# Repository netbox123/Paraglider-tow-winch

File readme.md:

# Paraglider Tow Winch

Version 0.2

An open-source electric tow winch for paragliding, designed with safety, reliability and maintainability as the primary goals.

The project combines:

- Parametric mechanical design in FreeCAD
- Python-generated CAD models
- Direct rope tension measurement using a load cell
- PID-controlled electric drive
- Automatic level winding using a self-reversing traverse screw
- Open documentation and engineering calculations

## Project Goals

The aim is to build a tow winch that:

- Maintains constant tow force independent of drum diameter.
- Winds the rope neatly during both retrieval and payout.
- Minimizes side loads on the level wind mechanism.
- Is easy to maintain using commercially available components.
- Can be reproduced and improved by other clubs.

## Current Concept

### Frame

- 1500 × 800 × 800 mm
- 50 × 50 × 4 mm square steel tube

### Drum

- Width: 250 mm
- Core diameter: 390 mm
- Flange diameter: 590 mm
- 5 mm steel shell
- 5 mm steel flanges
- 50 mm shaft
- Internal stiffening discs

### Power

Planned motor:

- QS165 12 kW
- 2.37:1 gearbox

### Rope

- 3 mm Dyneema
- Approximately 1500 m
- Typical tow tension: 40–100 kg

### Level Wind

A mechanically synchronized self-reversing traverse screw ("diamond screw" or "level wind screw") is used instead of a stepper motor.

Advantages:

- Works automatically in both winding directions.
- Always remains synchronized with the drum.
- No electronic positioning required.

### Tension Control

Tow force will be measured directly with a load cell mounted beneath the moving guide pulley.

Benefits:

- Direct measurement of rope tension.
- Independent of drum diameter.
- Independent of gearbox efficiency.
- Independent of motor current.
- Improved PID control.

## Software

The FreeCAD model is generated from Python macros (`freecad/`), one module per subsystem, all driven from a single [`config.py`](freecad/config.py).

The intention is that the complete winch can be regenerated from a small set of configuration parameters.

Modules built so far:

- Frame (hollow mitred tube)
- Battery boxes
- Drum (barrel, flanges, shaft, bearings)
- Motor mount and chain drivetrain (motor, sprockets)
- Rope intake (self-aligning swivel, rollers, guide wheels, line cutter)
- Level wind (Hiwin linear rail, self-reversing screw, flange bearings)
- Winding pulley and load cell mount (rod-end pivot)
- Operator-display panel-mount frame ([`gigadisplay_holder/`](gigadisplay_holder/) - a separate small parametric part, 3D-printed, fitted to the real GIGA Display Shield)

Still open:

- Electronics firmware - mainboard PCB (ESP32-S3) is designed, placed, routed and ready to order (see [docs/electronics.md](docs/electronics.md)); firmware itself has only a first communications skeleton so far, no control logic yet (see [docs/software.md](docs/software.md))
- CAN vs. analog throttle control - Fardriver's CAN61 protocol spec is in hand but not yet confirmed on real hardware; analog throttle kept as the wired fallback either way
- Frame cross-member mitres
- Motor mount bracket (currently a placeholder)

### Running the model

1. Install [FreeCAD](https://www.freecad.org/) (1.1 or newer).
2. Open FreeCAD and use **Macro → Macros… → Execute** to run [`freecad/main.py`](freecad/main.py), or open it in the built-in Python console and run it directly.
3. [`main.py`](freecad/main.py) creates a new `TowWinch` document and builds the complete model from [`config.py`](freecad/config.py). Edit values in [`config.py`](freecad/config.py) and re-run the macro to regenerate the model.

The model can also be regenerated headless (no GUI) with `freecadcmd freecad/main.py`, useful for scripted checks.

The operator-display frame in [`gigadisplay_holder/`](gigadisplay_holder/) is a self-contained parametric part with its own `config.py`; build it with `freecadcmd gigadisplay_holder/build.py`. See its [README](gigadisplay_holder/README.md).

## Status

The FreeCAD model is parametric and covers the mechanical structure end-to-end: frame, drum, drivetrain, rope intake and level wind. The electronics mainboard (ESP32-S3) is fully designed - schematic and PCB placed/routed, ready to order (see [docs/electronics.md](docs/electronics.md)). Firmware work has started: the GIGA/pilot-handheld JSON protocol is defined and a first communications-only skeleton exists (see [docs/software.md](docs/software.md), [`firmware/esp32_mainboard/`](firmware/esp32_mainboard/)) - the real control system (PID, CAN61, sensors) is not built yet.

Fabrication of the frame has already started in parallel with the CAD work (see [docs/build_log.md](docs/build_log.md)).

See [docs/todo.md](docs/todo.md) for the detailed, up-to-date task list.

## Documentation

- [Mission statement](docs/mission_statement.md)
- [History and design philosophy](docs/history.md)
- [Control philosophy](docs/control_philosophy.md)
- [Electronics architecture](docs/electronics.md)
- [Software architecture](docs/software.md)
- [Design decisions](docs/design_decisions.md)
- [Rope / drive train calculations](docs/rope_calculations.md)
- [Build log](docs/build_log.md)
- [Todo list](docs/todo.md)

## Contributions

Suggestions, calculations and constructive criticism are welcome.

The goal is to produce a safe, well-documented tow winch that can be used and improved by the paragliding community.

---

*Work in progress.*

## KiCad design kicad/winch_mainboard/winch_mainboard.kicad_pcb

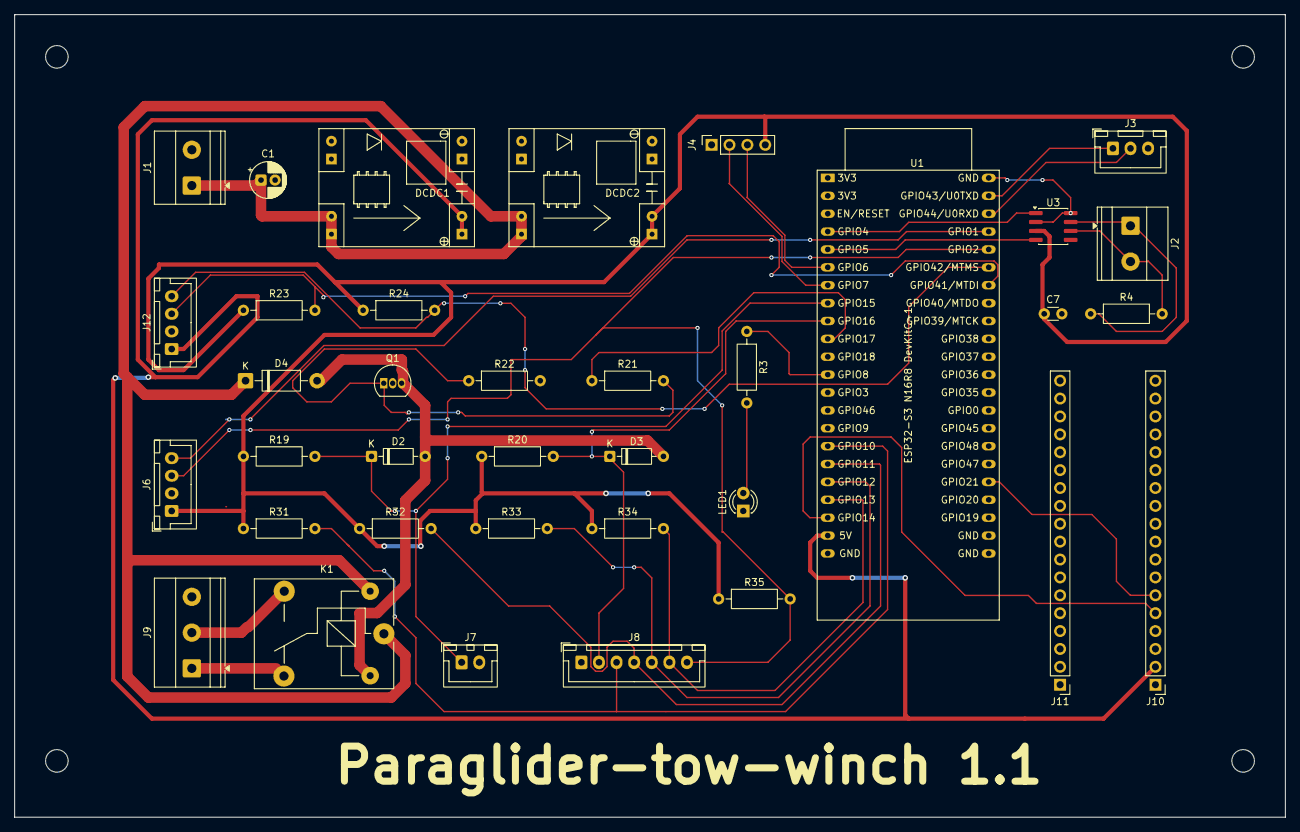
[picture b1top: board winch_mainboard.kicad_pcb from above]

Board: 2 copper layers, 180.5 x 114.0 mm, 40 parts (0 on the bottom side), 31 nets.

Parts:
C1: 10uF/35V; CP_Radial_D5.0mm_P2.00mm
C7: 100nF; C_Disc_D3.0mm_W1.6mm_P2.50mm
D2, D3: 1N4148; D_DO-35_SOD27_P7.62mm_Horizontal
D4: 1N4007 (flyback); D_DO-41_SOD81_P10.16mm_Horizontal
DCDC1: DCDC 24V->5V MP1584; MP1584_buck_module
DCDC2: DCDC 24V->3V3 MP1584; MP1584_buck_module
J1: PWR_IN_24V; TerminalBlock_Phoenix_MKDS-1,5-2-5.08_1x02_P5.08mm_Horizont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
J2: CAN_BUS Fardriver; TerminalBlock_Phoenix_MKDS-1,5-2-5.08_1x02_P5.08mm_Horizont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
J3: GIGA UART (TXD,RXD,GND); JST_XH_B3B-XH-A_1x03_P2.50mm_Vertical
J4: HX711 module; PinSocket_1x04_P2.54mm_Vertical
J6: Spare I/O; JST_XH_B4B-XH-A_1x04_P2.50mm_Vertical
J7: Line cut switch; JST_XH_B2B-XH-A_1x02_P2.50mm_Vertical
J8: Winchman remote switches; JST_XH_B7B-XH-A_1x07_P2.50mm_Vertical
J9: Cut motor out (24V); TerminalBlock_Phoenix_MKDS-1,5-3-5.08_1x03_P5.08mm_Horizont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
J10, J11: Heltec; PinHeader_1x18_P2.54mm_Vertical
J12: Hall sensors drum; JST_XH_B4B-XH-A_1x04_P2.50mm_Vertical
K1: Songle SRD-24VDC-SL-C; Relay_SPDT_SANYOU_SRD_Series_Form_C
LED1: Status; LED_D3.0mm
MH1, MH2, MH3, MH4: M3; MountingHole_3.2mm_M3
Q1: BC337-40; TO-92_Inline
R3: 330R; R_Axial_DIN0207_L6.3mm_D2.5mm_P10.16mm_Horizontal
R4: 120R (termination); R_Axial_DIN0207_L6.3mm_D2.5mm_P10.16mm_Horizontal
R19, R20, R31, R32, R33, R34, R35: 10k; R_Axial_DIN0207_L6.3mm_D2.5mm_P10.16mm_Horizontal
R21, R23, R24: 4.7k; R_Axial_DIN0207_L6.3mm_D2.5mm_P10.16mm_Horizontal
R22: 100k; R_Axial_DIN0207_L6.3mm_D2.5mm_P10.16mm_Horizontal
U1: ESP32-S3 N16R8 DevKitC-1; ESP32-S3-DevKitC
U3: SN65HVD230; SOIC-8_3.9x4.9mm_P1.27mm

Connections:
+3V3: C7.1, DCDC2.4, J4.4, J6.1, R19.1, R20.1, R23.1, R24.1, R31.1, R32.1, R33.1, R34.1, R35.1, U3.3
+5V: DCDC1.4, J10.2, J12.1, U1.21
+24V: C1.1, D4.1, DCDC1.1, DCDC2.1, J1.1, K1.1, K1.2
CAN_H: J2.1, R4.1, U3.7
CAN_L: J2.2, R4.2, U3.6
CAN_RX: U1.5, U3.4
CAN_TX: U1.4, U3.1
CUT_MOTOR_A: J9.1, K1.4
CUT_MOTOR_B: J9.2, K1.3
CUT_Q1_BASE: Q1.1, R21.2, R22.1
CUT_RELAY_DRIVE: R21.1, U1.10
CUT_SW1_SENSE: D2.1, J7.1, R19.2, U1.8
CUT_SW2_SENSE: D3.1, J8.2, R20.2, U1.9
ESP32_RXD: J3.2, U1.42
ESP32_TXD: J3.1, U1.43
ESTOP_SENSE: J8.3, R31.2, U1.16
GND: C1.2, C7.2, DCDC1.2, DCDC1.3, DCDC2.2, DCDC2.3, J1.2, J3.3, J4.1, J6.2, J7.2, J8.1, J9.3, J10.1, J12.2, LED1.1, Q1.2, R22.2, U1.22, U1.23, U1.24, U1.44, U3.2, U3.8
HALL_A: J12.3, R23.2, U1.38
HALL_B: J12.4, R24.2, U1.39
HX711_DT: J4.2, U1.7
HX711_SCK: J4.3, U1.6
LED1_A: LED1.2, R3.2
LED_STATUS: R3.1, U1.12
LORA_RXD: J10.6, U1.27
LORA_TXD: J10.5, U1.20
RELAY_COIL_LOW: D2.2, D3.2, D4.2, K1.5, Q1.3
SPARE_GPIO1: J6.4, U1.41
SPARE_GPIO2: J6.3, J8.7, R35.2, U1.40
TENSION_DOWN_SENSE: J8.5, R33.2, U1.18
TENSION_RESET_SENSE: J8.6, R34.2, U1.19
TENSION_UP_SENSE: J8.4, R32.2, U1.17

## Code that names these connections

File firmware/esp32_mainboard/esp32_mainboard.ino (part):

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static const int PIN_HELTEC_TXD = 14;  // ESP32 -> Heltec RXD
static const int PIN_HELTEC_RXD = 21;  // ESP32 <- Heltec TXD
// GIGA link uses hardware UART0 (GPIO43/44) via Serial0 - fixed pins, no remap.
static const int PIN_ESTOP_SENSE = 10;  // active-low, winchman remote e-stop switch
static const int PIN_STATUS_LED = 48;   // onboard addressable RGB LED (DevKitC-1)

// Physical "release" trigger - lets the winchman end a tow cleanly by hand,
// without depending on the GIGA link (see docs/software.md "Field authority":
// state_cmd is otherwise GIGA-only). Wired to J8 (winchman remote, 7-pin)
// pin 7 / SPARE_GPIO2, with its own dedicated 10k pull-up (R35, see
// docs/electronics.md) - same convention as the other four winchman-remote
// switches, not an internal-pull-up-only bodge. GPIO1 (still reachable via
// J6, the spare-I/O connector) remains free for a future addition.
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// yet - these two meanings would apply in disjoint states (READY vs.
// NORMAL_TOW) if/when that one is built, same non-conflicting-reuse
// pattern as the +5kg/-5kg buttons already use.
static const int PIN_TENSION_RESET_SENSE = 13;

// ---------------------------------------------------------------------------
// Timing
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// redundant there, but makes bench-testing this file alone easier (a bare
// wire to GND simulates a press, no external resistor needed).
bool estopSwitchPressed() {
  return digitalRead(PIN_ESTOP_SENSE) == LOW;
}

// Active-low, same convention as the e-stop switch above.
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}

bool tensionResetSwitchPressed() {
  return digitalRead(PIN_TENSION_RESET_SENSE) == LOW;
}

// ---------------------------------------------------------------------------
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  Serial.begin(115200);   // USB-CDC, debug console only (see board-setting note above)
  Serial0.begin(115200);  // GIGA UART, native UART0 pins (GPIO43/44)
  Serial1.begin(115200, SERIAL_8N1, PIN_HELTEC_RXD, PIN_HELTEC_TXD);  // Heltec UART
  pinMode(PIN_ESTOP_SENSE, INPUT_PULLUP);
  pinMode(PIN_RELEASE_SENSE, INPUT_PULLUP);
  pinMode(PIN_TENSION_PLUS_SENSE, INPUT_PULLUP);
  pinMode(PIN_TENSION_MINUS_SENSE, INPUT_PULLUP);
  pinMode(PIN_TENSION_RESET_SENSE, INPUT_PULLUP);

  Serial.println("ESP32 mainboard - comms skeleton starting");

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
